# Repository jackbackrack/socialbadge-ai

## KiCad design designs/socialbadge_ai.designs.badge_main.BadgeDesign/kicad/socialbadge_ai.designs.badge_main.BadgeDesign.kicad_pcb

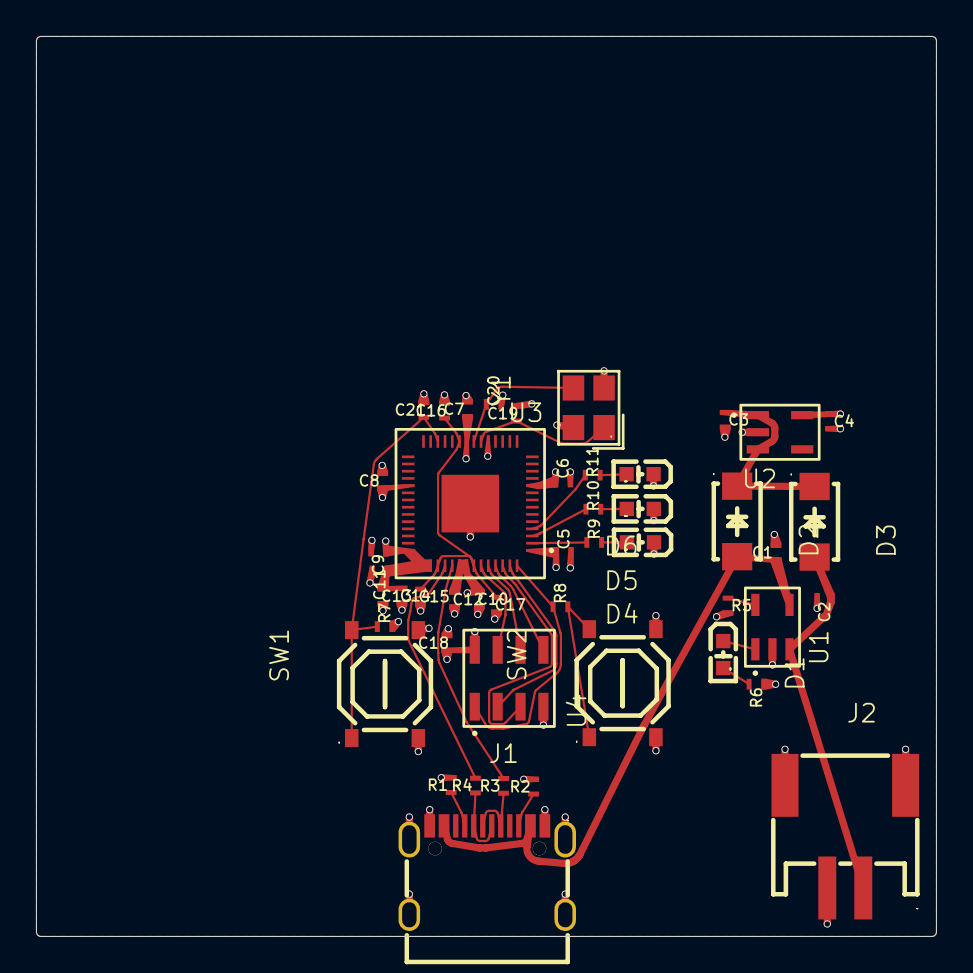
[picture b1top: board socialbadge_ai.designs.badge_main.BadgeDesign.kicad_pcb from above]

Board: 4 copper layers, 50.0 x 50.0 mm, 47 parts (0 on the bottom side), 31 nets.

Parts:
C1: 4.7 µF; LANDPATTERN0402_4
C2: 4.7 µF; LANDPATTERN0402_5
C3: 1 µF; LANDPATTERN0402_8
C4: 1 µF; LANDPATTERN0402_9
C5: 100 nF; LANDPATTERN0402_10
C6: 100 nF; LANDPATTERN0402_11
C7: 100 nF; LANDPATTERN0402_12
C8: 100 nF; LANDPATTERN0402_13
C9: 100 nF; LANDPATTERN0402_14
C10: 100 nF; LANDPATTERN0402_15
C11: 100 nF; LANDPATTERN0402_16
C12: 100 nF; LANDPATTERN0402_17
C13: 1 µF; LANDPATTERN0402_18
C14: 100 nF; LANDPATTERN0402_19
C15: 1 µF; LANDPATTERN0402_20
C16: 100 nF; LANDPATTERN0402_21
C17: 100 nF; LANDPATTERN0402_22
C18: 100 nF; LANDPATTERN0402_23
C19: 27 pF; LANDPATTERN0402_24
C20: 27 pF; LANDPATTERN0402_25
C21: 100 nF; LANDPATTERN0402_27
D1: KT-0603R; Pkg_LP_1
D2: SS14; Pkg_LP_2
D3: SS14; Pkg_LP_3
D4: KT-0603R; Pkg_LP_7
D5: KT-0603R; Pkg_LP_8
D6: KT-0603R; Pkg_LP_9
J1: TYPE-C-31-M-12; Pkg_LP
J2: 2.0-2P WT; Pkg_LP_10
R1: 5.1 kΩ; LANDPATTERN0402
R2: 5.1 kΩ; LANDPATTERN0402_1
R3: 27 Ω; LANDPATTERN0402_2
R4: 27 Ω; LANDPATTERN0402_3
R5: 2 kΩ; LANDPATTERN0402_6
R6: 1 kΩ; LANDPATTERN0402_7
R7: 10 kΩ; LANDPATTERN0402_26
R8: 1 kΩ; LANDPATTERN0402_28
R9: 330 Ω; LANDPATTERN0402_29
R10: 330 Ω; LANDPATTERN0402_30
R11: 330 Ω; LANDPATTERN0402_31
SW1: TS-1187A-B-A-B; Pkg_LP_5
SW2: TS-1187A-B-A-B; Pkg_LP_6
U1: MCP73831T-2ACI/OT; SOT23_5
U2: AP2112K-3.3TRG1; SOT23_5_1
U3: RP2040; QFN
U4: W25Q128JVSIQ; SOIC
Y1: X322512MSB4SI; Pkg_LP_4

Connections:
1V1: C15.1, C16.1, C17.1, U3.23, U3.45, U3.50
3V3: C4.1, C5.1, C6.1, C7.1, C8.1, C9.1, C10.1, C11.1, C12.1, C13.1, C14.1, C18.1, R6.1, R7.2, U2.5, U3.1, U3.10, U3.22, U3.33, U3.42, U3.43, U3.44, U3.48, U3.49, U4.8
BOOTSEL_NODE: R8.2, SW2.1, SW2.2
CHG_STAT: D1.1, U1.1
GND: C1.2, C2.2, C3.2, C4.2, C5.2, C6.2, C7.2, C8.2, C9.2, C10.2, C11.2, C12.2, C13.2, C14.2, C15.2, C16.2, C17.2, C18.2, C19.2, C20.2, C21.2, D4.1, D5.1, D6.1, J1.9, J1.10, J1.13, J1.14, J1.15, J1.16, J2.2, J2.3, J2.4, R1.2, R2.2, R5.2, SW1.3, SW1.4, SW2.3, SW2.4, U1.2, U2.2, U3.19, U3.thermal_pads0, U4.4, Y1.2, Y1.3
GPIO[0]: R9.1, U3.2
GPIO[1]: R10.1, U3.3
GPIO[2]: R11.1, U3.4
PROG: R5.1, U1.5
QSPI_CSn: R8.1, U3.56, U4.1
QSPI_SCLK: U3.52, U4.6
QSPI_SD0: U3.53, U4.5
QSPI_SD1: U3.55, U4.2
QSPI_SD2: U3.54, U4.3
QSPI_SD3: U3.51, U4.7
RUN: C21.1, R7.1, SW1.1, SW1.2, U3.26
SYS: C3.1, D2.2, D3.2, U2.1, U2.3
USB_DM: R4.2, U3.46
USB_DN: J1.3, J1.5, R4.1
USB_DP: J1.4, J1.6, R3.1
VBAT: C2.1, D3.1, J2.1, U1.3
VBUS: C1.1, D2.1, J1.11, J1.12, U1.4
XIN: C19.1, U3.20, Y1.1
XOUT: C20.1, U3.21, Y1.4
mcu_USB_DP: R3.2, U3.47
p1: J1.8, R2.1
p2: D1.2, R6.2
r_cc1_p1: J1.2, R1.1
r_leds[0]_p2: D4.2, R9.2
r_leds[1]_p2: D5.2, R10.2
r_leds[2]_p2: D6.2, R11.2

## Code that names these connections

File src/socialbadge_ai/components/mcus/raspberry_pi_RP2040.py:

"""
Raspberry Pi RP2040 Dual ARM Cortex-M0+ Microcontroller

QFN-56 package, 7x7mm, 0.4mm pitch with reduced 3.2x3.2mm ePad.

Pin map and dimensions sourced from RP2040 datasheet
(https://datasheets.raspberrypi.com/rp2040/rp2040-datasheet.pdf):
- Pin list: section 5.5.2.2 (Tables 615-621), pages 612-614
- Recommended PCB footprint: section 5.1.2 (Figure 167), page 608
"""

import jitx
from jitx import PadMapping
from jitx.net import Port
from jitx.toleranced import Toleranced
from jitx.shapes.composites import rectangle
from jitxlib.jlcpcb import LCSCPart
from jitxlib.landpatterns.generators.qfn import QFN, QFNLead
from jitxlib.landpatterns.leads import LeadProfile
from jitxlib.landpatterns.package import RectanglePackage
from jitxlib.landpatterns.ipc import DensityLevel
from jitxlib.landpatterns.pads import SMDPadConfig, WindowSubdivide
from jitxlib.symbols.box import BoxSymbol, PinGroup, Row, Column


class RP2040(jitx.Component):
    """RP2040 microcontroller — dual Cortex-M0+ at 133 MHz, 264 KB SRAM,
    30 GPIO (4 ADC-capable), QSPI external flash interface, USB 1.1."""

    mpn = "RP2040"
    manufacturer = "Raspberry Pi"
    reference_designator_prefix = "U"
    lcsc = LCSCPart("C2040")
    datasheet = "https://datasheets.raspberrypi.com/rp2040/rp2040-datasheet.pdf"

    # Power supplies
    IOVDD = [Port() for _ in range(6)]    # pins 1, 10, 22, 33, 42, 49
    DVDD = [Port() for _ in range(2)]     # pins 23, 50
    USB_VDD = Port()                       # pin 48
    ADC_AVDD = Port()                      # pin 43
    VREG_VIN = Port()                      # pin 44
    VREG_VOUT = Port()                     # pin 45
    GND = Port()                           # central ePad (pin 57)

    # 30 GPIOs; GPIO26-29 also serve as ADC0-3 (alt function on same pin)
    GPIO = [Port() for _ in range(30)]

    # Crystal oscillator
    XIN = Port()                           # pin 20
    XOUT = Port()                          # pin 21

    # Serial wire debug
    SWCLK = Port()                         # pin 24
    SWD = Port()                           # pin 25

    # Control / test
    RUN = Port()                           # pin 26
    TESTEN = Port()                        # pin 19, tie to GND

    # USB
    USB_DM = Port()                        # pin 46
    USB_DP = Port()                        # pin 47

    # QSPI flash interface
    QSPI_SD3 = Port()                      # pin 51
    QSPI_SCLK = Port()                     # pin 52
    QSPI_SD0 = Port()                      # pin 53
    QSPI_SD2 = Port()                      # pin 54
    QSPI_SD1 = Port()                      # pin 55
    QSPI_CSn = Port()                      # pin 56

    # QFN-56, 7x7mm body, 0.4mm pitch, reduced 3.2x3.2mm ePad
    landpattern = (
        QFN(num_leads=56)
        .lead_profile(
            LeadProfile(
                span=Toleranced.exact(7.0),
                pitch=0.4,
                type=QFNLead(
                    length=Toleranced.min_max(0.3, 0.5),
                    width=Toleranced.min_typ_max(0.13, 0.18, 0.23),
                ),
            ),
        )
        .package_body(
            RectanglePackage(
                width=Toleranced.exact(7.0),
                length=Toleranced.exact(7.0),
                height=Toleranced.min_max(0.8, 0.9),
            )
        )
        .thermal_pad(
            rectangle(3.2, 3.2),
            # Full-area paste on the exposed pad lets excess solder squeeze
            # out from under the package during reflow and bridge to a
            # perimeter pin; window it into a 2x2 grid per Raspberry Pi's
            # QFN-56 layout guidance instead.
            config=SMDPadConfig(paste=WindowSubdivide()),
        )
        .density_level(DensityLevel.C)
    )

    symbol = BoxSymbol(
        rows=Row(
            left=PinGroup(
                QSPI_CSn, QSPI_SCLK,
                QSPI_SD0, QSPI_SD1, QSPI_SD2, QSPI_SD3,
                XIN, XOUT,
                SWCLK, SWD,
                RUN, TESTEN,
                USB_DM, USB_DP,
            ),
            right=PinGroup(*GPIO),
        ),
        columns=Column(
            up=PinGroup(*IOVDD, *DVDD, USB_VDD, ADC_AVDD, VREG_VIN, VREG_VOUT),
            down=PinGroup(GND),
        ),
    )

    def __init__(self):
        lp = self.landpattern
        self.mappings = [PadMapping({
            self.IOVDD[0]: [lp.p[1]],
            self.GPIO[0]: [lp.p[2]],
            self.GPIO[1]: [lp.p[3]],
            self.GPIO[2]: [lp.p[4]],
            self.GPIO[3]: [lp.p[5]],
            self.GPIO[4]: [lp.p[6]],
            self.GPIO[5]: [lp.p[7]],
            self.GPIO[6]: [lp.p[8]],
            self.GPIO[7]: [lp.p[9]],
            self.IOVDD[1]: [lp.p[10]],
            self.GPIO[8]: [lp.p[11]],
            self.GPIO[9]: [lp.p[12]],
            self.GPIO[10]: [lp.p[13]],
            self.GPIO[11]: [lp.p[14]],
            self.GPIO[12]: [lp.p[15]],
            self.GPIO[13]: [lp.p[16]],
            self.GPIO[14]: [lp.p[17]],
            self.GPIO[15]: [lp.p[18]],
            self.TESTEN: [lp.p[19]],
            self.XIN: [lp.p[20]],
            self.XOUT: [lp.p[21]],
            self.IOVDD[2]: [lp.p[22]],
            self.DVDD[0]: [lp.p[23]],
            self.SWCLK: [lp.p[24]],
            self.SWD: [lp.p[25]],
            self.RUN: [lp.p[26]],
            self.GPIO[16]: [lp.p[27]],
            self.GPIO[17]: [lp.p[28]],
            self.GPIO[18]: [lp.p[29]],
            self.GPIO[19]: [lp.p[30]],
            self.GPIO[20]: [lp.p[31]],
            self.GPIO[21]: [lp.p[32]],
            self.IOVDD[3]: [lp.p[33]],
            self.GPIO[22]: [lp.p[34]],
            self.GPIO[23]: [lp.p[35]],
            self.GPIO[24]: [lp.p[36]],
            self.GPIO[25]: [lp.p[37]],
            self.GPIO[26]: [lp.p[38]],
            self.GPIO[27]: [lp.p[39]],
            self.GPIO[28]: [lp.p[40]],
            self.GPIO[29]: [lp.p[41]],
            self.IOVDD[4]: [lp.p[42]],
            self.ADC_AVDD: [lp.p[43]],
            self.VREG_VIN: [lp.p[44]],
            self.VREG_VOUT: [lp.p[45]],
            self.USB_DM: [lp.p[46]],
            self.USB_DP: [lp.p[47]],
            self.USB_VDD: [lp.p[48]],
            self.IOVDD[5]: [lp.p[49]],
            self.DVDD[1]: [lp.p[50]],
            self.QSPI_SD3: [lp.p[51]],
            self.QSPI_SCLK: [lp.p[52]],
            self.QSPI_SD0: [lp.p[53]],
            self.QSPI_SD2: [lp.p[54]],
            self.QSPI_SD1: [lp.p[55]],
            self.QSPI_CSn: [lp.p[56]],
            self.GND: [lp.thermal_pads[0]],
        })]


Device: type[RP2040] = RP2040
